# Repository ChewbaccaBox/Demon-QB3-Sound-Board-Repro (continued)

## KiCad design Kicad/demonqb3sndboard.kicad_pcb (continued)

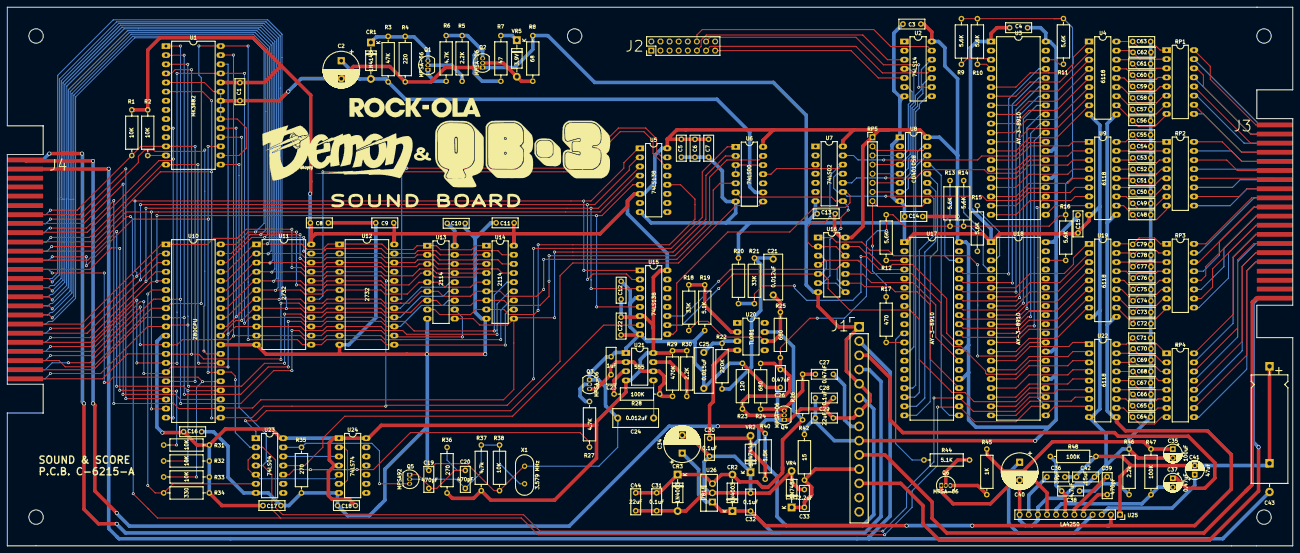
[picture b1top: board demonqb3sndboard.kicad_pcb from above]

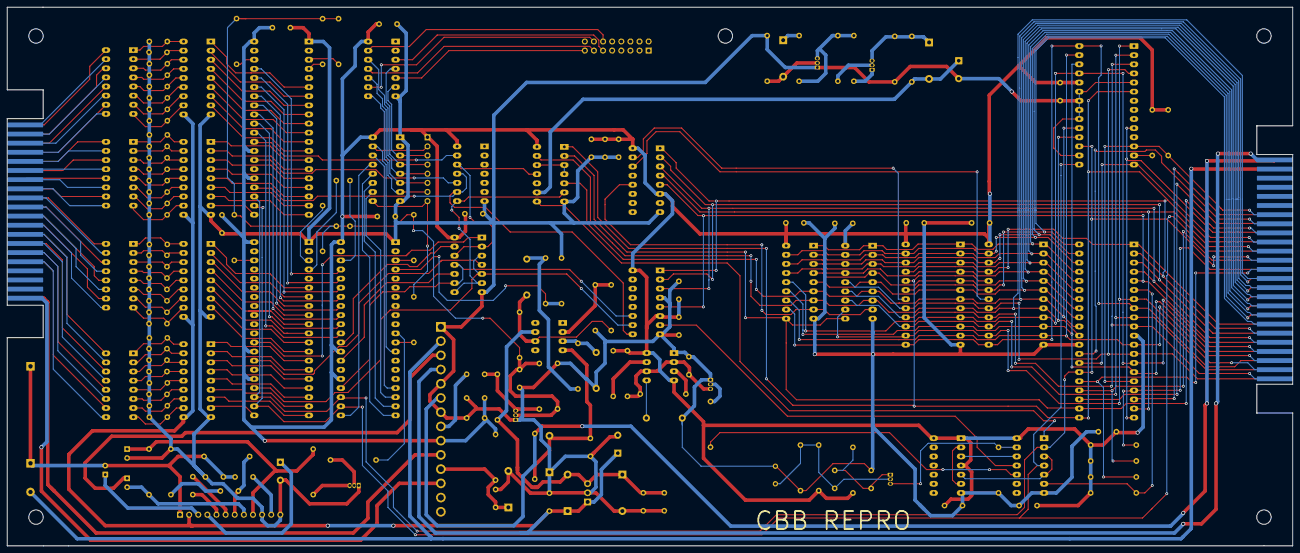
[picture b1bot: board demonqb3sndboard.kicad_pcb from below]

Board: 2 copper layers, 358.0 x 150.0 mm, 169 parts (2 on the bottom side), 238 nets.

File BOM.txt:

C1 		Right of MK3880			Orange
    C2		47uF				Electrolytic
    C3		Top Left of U2			Blue
    C4		Above U3			
    C5		Left of u6			
    C6		Left of u6			
    C7 		beside u7			
    C8		above u11 (if installed)	
    C9 		above u12			
    C10 	above u13			
    C11 	above u14			
    C12		beside U15			
    C13		above u16			
    C14		above u17			
    C15		Right of R10			
    C16		Below z80			Blue
    C17		above u23			Blue
    C18		above u24			
    C22		above 555


    C19		470pF
    C20		470pF
    C21		0.012uF
    C23		1uF
    C24		0.012uF
    C25		0.015uF
    C26		0.47uF
    C27		0.47uF
    C28		0.1uF
    C29		22uF
    C30		0.1uF
    C31		0.1uF
    C32		0.1uF
    C33		2.2uF
    C34		470uF
    C35		100uF
    C36		39pF
    C37		0.47uF
    C38		4.7uF
    C39		470pF
    C40		470uF
    C41		47uF
    C42		.15uF
    C43		1000uF
    C44		22nF
    C45		above u19
    C46		above u22

    C47		?

    C48 - C79   =   CA1 - CA32





    CA1		220pF
    CA2		220pF
    CA3		220pF
    CA4		220pF
    CA5		220pF
    CA6		220pF
    CA7		220pF
    CA8		220pF
    CA9		220pF
    CA10	220pF
    CA11	220pF
    CA12	220pF
    CA13	220pF
    CA14	220pF
    CA15	220pF
    CA16	220pF
    CA17	220pF
    CA18	220pF
    CA19	220pF
    CA20	220pF
    CA21	220pF
    CA22	220pF
    CA23	220pF
    CA24	220pF
    CA25	220pF
    CA26	220pF
    CA27	220pF
    CA28	220pF
    CA29	220pF
    CA30	220pF
    CA31	220pF
    CA32	220pF



    CR1		1N4148
    CR2		1N4003
    CR3		1N4003



    J1		14 pin .156 header, 1 x 14
    J2		16 pin .1 header, 2 x 8
    J3		(Edge connector, part of PCB already)
    J4		(Edge connector, part of PCB already)

Transistors
	5 * MPSA06, 1 * MPSA92

    Q1		MPSA06
    Q2		MPSA06
    Q3		MPSA06
    Q4		MPSA06
    Q5		MPSA92
    Q6		MPSA06



Resistors


    R1		10K
    R2		10K
    R3		47K
    R4		220
    R5		47K
    R6		4.7K
    R7		47K
    R8		68
    R9		5.6K
    R10		5.6K
    R11		5.6K
    R12		5.6K
    R13		5.6K
    R14		5.6K
    R15		5.6K
    R16		5.6K
    R17		470
    R18		33K
    R19		5.1K
    R20		1K
    R21		33K
    R22		220K
    R23		120
    R24		680
    R25		680
    R26		1K
    R27		4.7K
    R28		100K
    R29		470K
    R30		2.2K
    R31		10K
    R32		10K
    R33		10K
    R34		330
    R35		270
    R36		270
    R37		4.7k
    R38		10K
    R40		1.5K
    R42		15
    R44		5.1K
    R45		1K
    R46		2.2k
    R47		100K
    R48		100K
    RP1		R_Pack08
    RP2		R_Pack08
    RP3		R_Pack08
    RP4		R_Pack08
    RP5		100K


Chips / Packages
	3 * AY-3-8910, 2 * 2114, 2 * 2732, 1 * Z80, 1 * Z

    U1		MK3882
    U2		74LS14
    U3		AY-3-8910
    U4		6118
    U5		74LS138
    U6		74LS00
    U7		74LS02
    U8		CD40105B
    U9		6118
    U10		Z80CPU
    U11		2732
    U12		2732
    U13		2114
    U14		2114
    U15		74LS138
    U16		74LS02
    U17		AY-3-8910
    U18		AY-3-8910
    U19		6118
    U20		TL081
    U21		555
    U22		6118
    U23		74LS04
    U24		74LS74
    U25		LA4250
    U26		7815
    VR2		1N4744A
    VR4		1N748A
    VR5		?

Crystals
	1 * 3.579 MHz

    X1		3.579 MHz


chips

3 x AY-3-8910
1 x LA4250
1 x TL081
2 x 2114
1 x 2732	
1 x CD40105B
1 x Z80
1 x Z80-CTC

1 x 74LS00
2 x 74LS02
1 x 74LS04
1 x 74LS14
1 x 74LS74
2 x 74LS138

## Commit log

2022-06-01 Initial Commit
    Here's everything I've got so far.
